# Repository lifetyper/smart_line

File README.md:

就是个通过FT232H芯片，把USB转成SPI、I2C用于硬件调试的小工具，软件使用的是pyftdi。

第一版硬件有点小bug，但实际上使用时并不表现出来。

第二版改成kicad的开源工具了，很难用，所以凑合着用4层板画比较简单，反正嘉立创现在4层板才50块钱。。。。

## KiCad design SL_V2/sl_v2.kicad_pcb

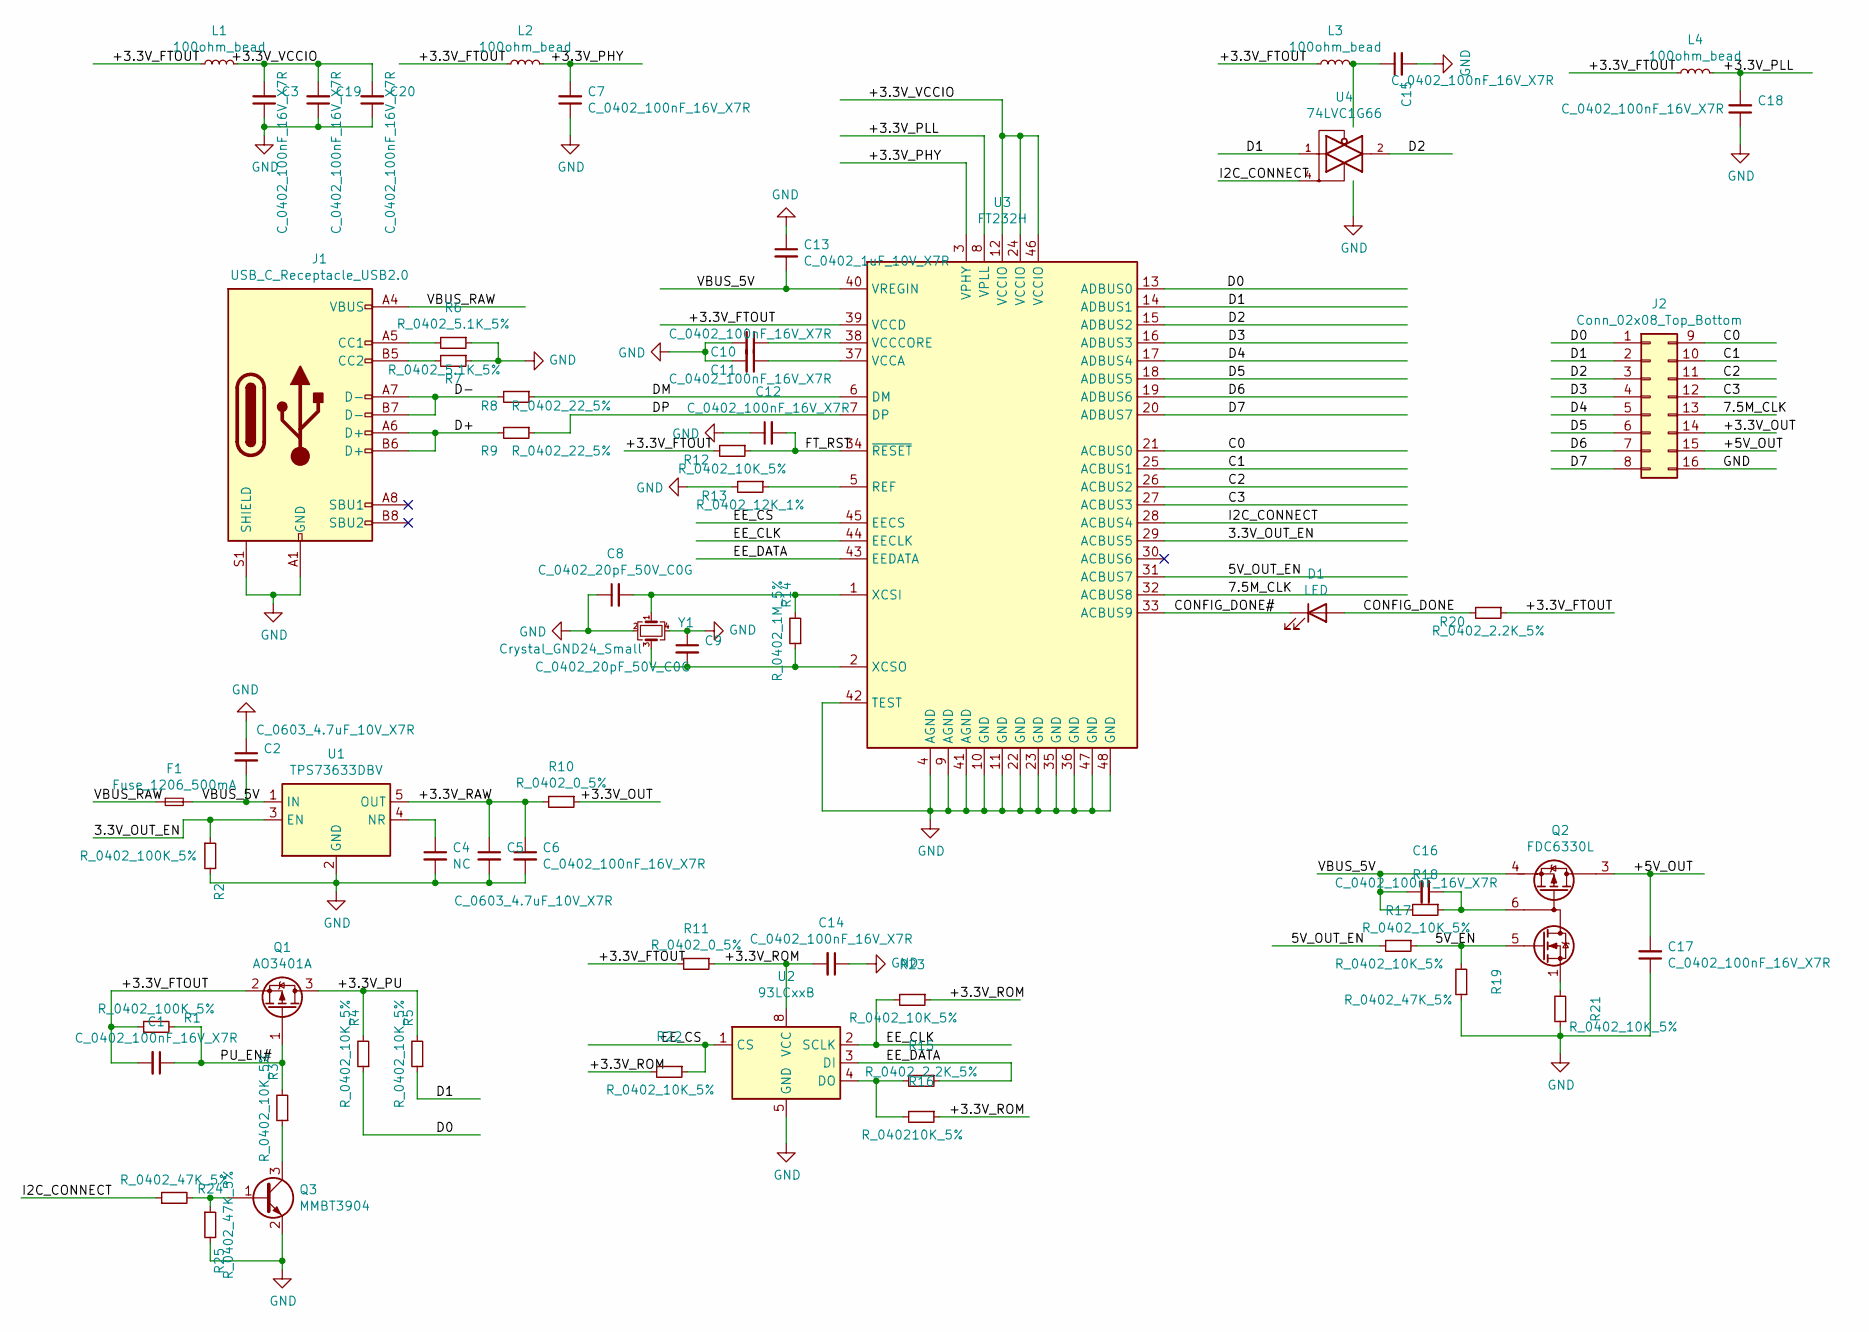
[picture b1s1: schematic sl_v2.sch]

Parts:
C1, C3, C6, C7, C10, C11, C12, C14, C15, C16, C17, C18, C19, C20: C_0402_100nF_16V_X7R; C_0402_1005Metric
C2, C5: C_0603_4.7uF_10V_X7R; C_0603_1608Metric
C4: NC; C_0402_1005Metric
C8, C9: C_0402_20pF_50V_C0G; C_0402_1005Metric
C13: C_0402_1uF_10V_X7R; C_0402_1005Metric
D1: LED; LED_0603_1608Metric
F1: Fuse_1206_500mA; Fuse_1206_3216Metric
J1: USB_C_Receptacle_USB2.0; USB_C_Receptacle_HRO_TYPE-C-31-M-12
J2: Conn_02x08_Top_Bottom; Connector_02X08_SMD_C
L1, L2, L3, L4: 100ohm_bead; L_0402_1005Metric
Q1: AO3401A; SOT-23
Q2: FDC6330L; TSOT-23-6
Q3: MMBT3904; SOT-23
R1, R2: R_0402_100K_5%; R_0402_1005Metric
R3, R4, R5, R12, R17, R18, R21, R22, R23: R_0402_10K_5%; R_0402_1005Metric
R6, R7: R_0402_5.1K_5%; R_0402_1005Metric
R8, R9: R_0402_22_5%; R_0402_1005Metric
R10, R11: R_0402_0_5%; R_0402_1005Metric
R13: R_0402_12K_1%; R_0402_1005Metric
R14: R_0402_1M_5%; R_0402_1005Metric
R15, R20: R_0402_2.2K_5%; R_0402_1005Metric
R16: R_040210K_5%; R_0402_1005Metric
R19, R24, R25: R_0402_47K_5%; R_0402_1005Metric
U1: TPS73633DBV; SOT-23-5
U2: 93LCxxB; SOIC-8_3.9x4.9mm_P1.27mm
U3: FT232H; LQFP-48_7x7mm_P0.5mm
U4: 74LVC1G66; SOT-353_SC-70-5
Y1: Crystal_GND24_Small; Oscillator_SMD_EuroQuartz_XO32-4Pin_3.2x2.5mm

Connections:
/3.3V_OUT_EN: R2.1, U1.3 (EN), U3.29 (ACBUS5)
/5V_EN: Q2.5 (G1), R17.1, R19.2
/5V_OUT_EN: R17.2, U3.31 (ACBUS7)
/7.5M_CLK: J2.13, U3.32 (ACBUS8)
/+3.3V_FTOUT: C1.2, L1.1, L2.1, L3.1, L4.1, Q1.2 (S), R1.1, R11.2, R12.2, R20.1, U3.39 (VCCD)
/+3.3V_PHY: C7.2, L2.2, U3.3 (VPHY)
/+3.3V_PLL: C18.2, L4.2, U3.8 (VPLL)
/+3.3V_PU: Q1.3 (D), R4.2, R5.2
/+3.3V_RAW: C5.1, C6.1, R10.2, U1.5 (OUT)
/+3.3V_ROM: C14.2, R11.1, R16.1, R22.2, R23.1, U2.8 (VCC)
/+3.3V_VCCIO: C3.2, C19.2, C20.2, L1.2, U3.12 (VCCIO), U3.24 (VCCIO), U3.46 (VCCIO)
/C0: J2.9, U3.21 (ACBUS0)
/C1: J2.10, U3.25 (ACBUS1)
/C2: J2.11, U3.26 (ACBUS2)
/C3: J2.12, U3.27 (ACBUS3)
/CONFIG_DONE: D1.2 (A), R20.2
/CONFIG_DONE#: D1.1 (K), U3.33 (ACBUS9)
/D0: J2.1, R4.1, U3.13 (ADBUS0)
/D1: J2.2, R5.1, U3.14 (ADBUS1), U4.1
/D2: J2.3, U3.15 (ADBUS2), U4.2
/D3: J2.4, U3.16 (ADBUS3)
/D4: J2.5, U3.17 (ADBUS4)
/D5: J2.6, U3.18 (ADBUS5)
/D6: J2.7, U3.19 (ADBUS6)
/D7: J2.8, U3.20 (ADBUS7)
/D+: J1.A6 (D+), J1.B6 (D+), R9.2
/D-: J1.A7 (D-), J1.B7 (D-), R8.2
/DM: R8.1, U3.6 (DM)
/DP: R9.1, U3.7 (DP)
/EE_CLK: R23.2, U2.2 (SCLK), U3.44 (EECLK)
/EE_CS: R22.1, U2.1 (CS), U3.45 (EECS)
/EE_DATA: R15.1, U2.3 (DI), U3.43 (EEDATA)
/FT_RST: C12.2, R12.1, U3.34 (~RESET)
/I2C_CONNECT: R24.1, U3.28 (ACBUS4), U4.4
/PU_EN#: C1.1, Q1.1 (G), R1.2, R3.2
/VBUS_5V: C2.2, C13.2, C16.2, F1.2, Q2.4 (S2), R18.2, U1.1 (IN), U3.40 (VREGIN)
/VBUS_RAW: F1.1, J1.A4 (VBUS), J1.A9 (VBUS), J1.B4 (VBUS), J1.B9 (VBUS)
GND: C2.1, C3.1, C4.2, C5.2, C6.2, C7.1, C8.1, C9.1, C10.2, C11.2, C12.1, C13.1, C14.1, C15.2, C17.1, C18.1, C19.1, C20.1, J1.A1 (GND), J1.A12 (GND), J1.B1 (GND), J1.B12 (GND), J1.S1 (SHIELD), J2.16, Q3.2 (E), R2.2, R6.1, R7.1, R13.2, R19.1, R21.1, R25.2, U1.2 (GND), U2.5 (GND), U3.4 (AGND), U3.9 (AGND), U3.10 (GND), U3.11 (GND), U3.22 (GND), U3.23 (GND), U3.35 (GND), U3.36 (GND), U3.41 (AGND), U3.42 (TEST), U3.47 (GND), U3.48 (GND), U4.3 (GND), Y1.2, Y1.4
unnamed: C4.1, U1.4 (NR)
unnamed: C8.2, R14.2, U3.1 (XCSI), Y1.1
unnamed: C9.2, R14.1, U3.2 (XCSO), Y1.3
unnamed: C10.1, U3.38 (VCCCORE)
unnamed: C11.1, U3.37 (VCCA)
unnamed: C16.1, Q2.6 (D1), R18.1
unnamed: J1.A5 (CC1), R6.2
unnamed: J1.B5 (CC2), R7.2
unnamed: Q2.1 (S1), R21.2
unnamed: Q3.1 (B), R24.2, R25.1
unnamed: Q3.3 (C), R3.1
unnamed: R13.1, U3.5 (REF)
unnamed: R15.2, R16.2, U2.4 (DO)
VCC: C15.1, L3.2, U4.5 (VCC)

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
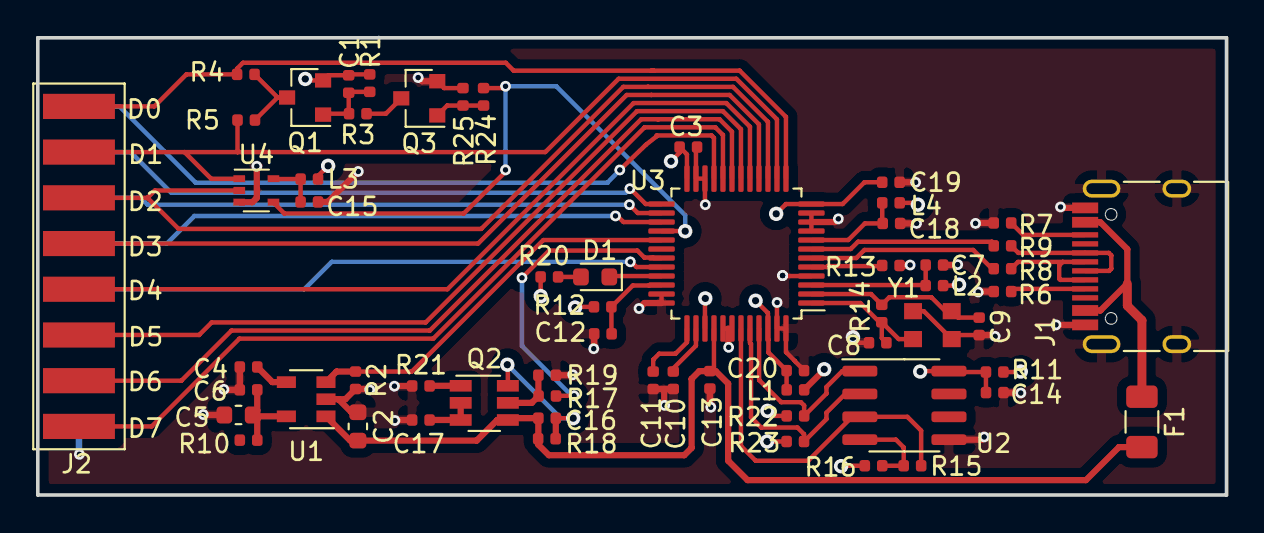
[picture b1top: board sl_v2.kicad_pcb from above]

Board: 4 copper layers, 66.0 x 25.4 mm, 61 parts (0 on the bottom side), 53 nets.

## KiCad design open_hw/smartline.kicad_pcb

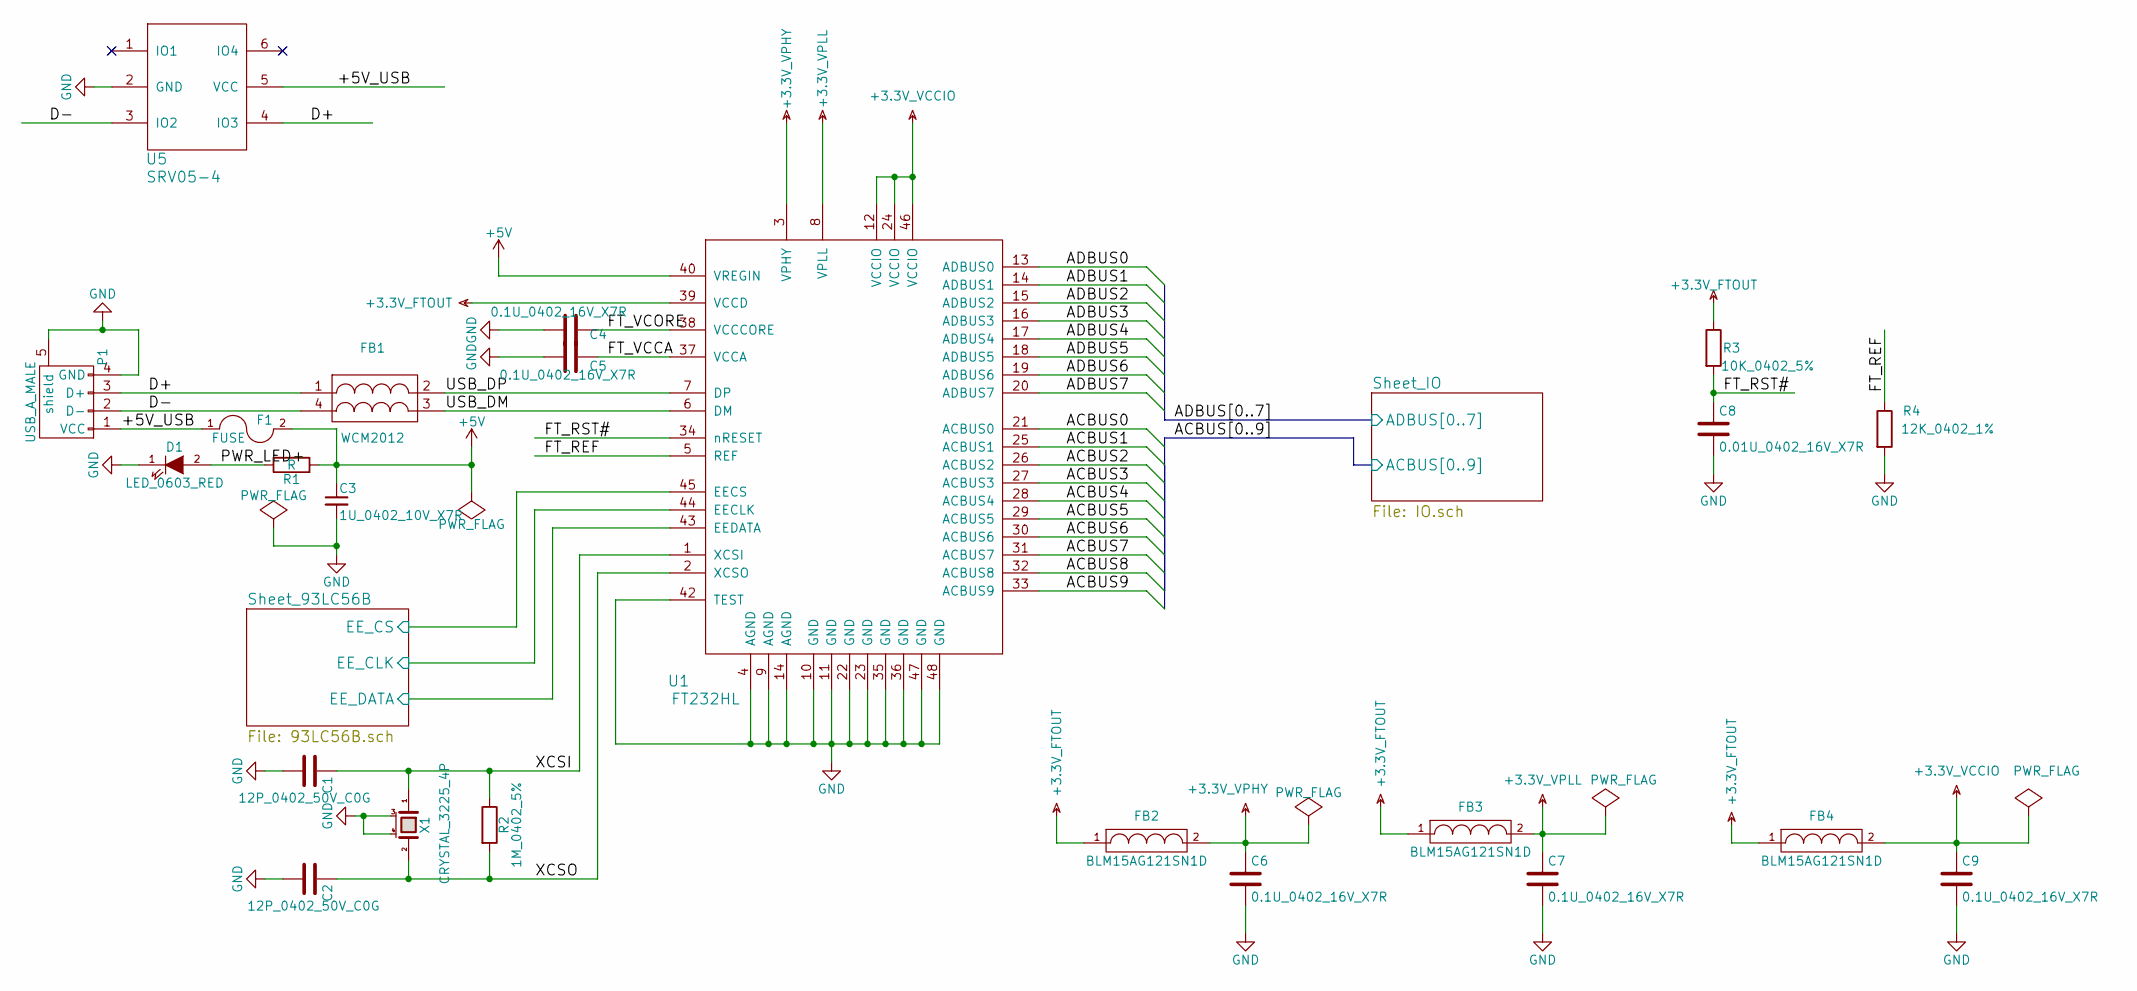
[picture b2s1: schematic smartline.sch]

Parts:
C1, C2: 12P_0402_50V_C0G; C_0402
C3: 1U_0402_10V_X7R; C_0402
C4, C5, C6, C7, C9: 0.1U_0402_16V_X7R; C_0402
C8: 0.01U_0402_16V_X7R; C_0402
D1: LED_0603_RED; LED_0603
F1: FUSE; Fuse_SMD1206_Reflow
FB1: WCM2012; WCM2012_4P
FB2, FB3, FB4: BLM15AG121SN1D; C_0402
P1: USB_A_MALE; USB_A_SMD
R1: R; R_0402
R2: 1M_0402_5%; R_0402
R3: 10K_0402_5%; R_0402
R4: 12K_0402_1%; R_0402
U1: FT232HL; LQFP-48_7x7mm_Pitch0.5mm
U5: SRV05-4; SOT-23-6
X1: CRYSTAL_3225_4P; Crystall_3225_4P

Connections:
+3.3V_FTOUT: FB2.1, FB3.1, FB4.1, R3.1, U1.39 (VCCD); also elsewhere on the board
+3.3V_VCCIO: C9.1, FB4.2, U1.12 (VCCIO), U1.24 (VCCIO), U1.46 (VCCIO)
+3.3V_VPHY: C6.1, FB2.2, U1.3 (VPHY)
+3.3V_VPLL: C7.1, FB3.2, U1.8 (VPLL)
+5V: C3.1, F1.2, R1.1, U1.40 (VREGIN); also elsewhere on the board
/+5V_USB: F1.1, P1.1 (VCC), U5.5 (VCC)
/ACBUS0: U1.21 (ACBUS0); also elsewhere on the board
/ACBUS1: U1.25 (ACBUS1); also elsewhere on the board
/ACBUS2: U1.26 (ACBUS2); also elsewhere on the board
/ACBUS3: U1.27 (ACBUS3); also elsewhere on the board
/ACBUS4: U1.28 (ACBUS4); also elsewhere on the board
/ACBUS5: U1.29 (ACBUS5); also elsewhere on the board
/ACBUS6: U1.30 (ACBUS6); also elsewhere on the board
/ACBUS7: U1.31 (ACBUS7); also elsewhere on the board
/ACBUS8: U1.32 (ACBUS8); also elsewhere on the board
/ACBUS9: U1.33 (ACBUS9); also elsewhere on the board
/ADBUS0: U1.13 (ADBUS0); also elsewhere on the board
/ADBUS2: U1.15 (ADBUS2); also elsewhere on the board
/ADBUS3: U1.16 (ADBUS3); also elsewhere on the board
/ADBUS4: U1.17 (ADBUS4); also elsewhere on the board
/ADBUS5: U1.18 (ADBUS5); also elsewhere on the board
/ADBUS6: U1.19 (ADBUS6); also elsewhere on the board
/ADBUS7: U1.20 (ADBUS7); also elsewhere on the board
/D+: FB1.1, P1.3 (D+), U5.4 (IO3)
/D-: FB1.4, P1.2 (D-), U5.3 (IO2)
/FT_REF: R4.1, U1.5 (REF)
/FT_RST#: C8.1, R3.2, U1.34 (nRESET)
/FT_VCCA: C5.1, U1.37 (VCCA)
/FT_VCORE: C4.1, U1.38 (VCCCORE)
/PWR_LED+: D1.2 (A), R1.2
/Sheet_93LC56B/EE_CLK: U1.44 (EECLK); also elsewhere on the board
/Sheet_93LC56B/EE_CS: U1.45 (EECS); also elsewhere on the board
/Sheet_93LC56B/EE_DATA: U1.43 (EEDATA); also elsewhere on the board
/USB_DM: FB1.3, U1.6 (DM)
/USB_DP: FB1.2, U1.7 (DP)
/XCSI: C1.1, R2.1, U1.1 (XCSI), X1.1
/XCSO: C2.1, R2.2, U1.2 (XCSO), X1.2

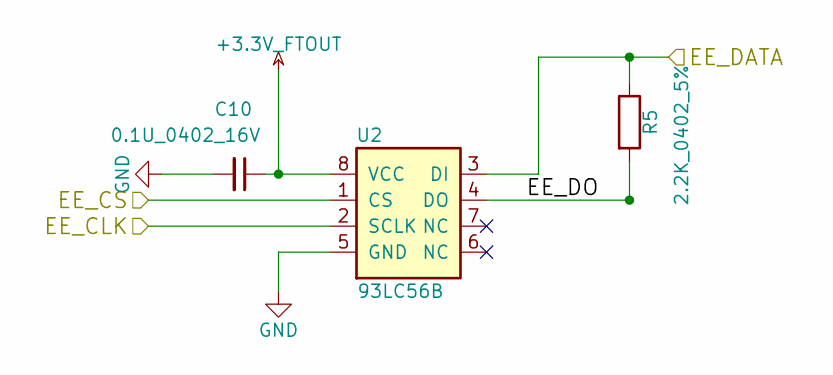
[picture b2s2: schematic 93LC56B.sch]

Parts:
C10: 0.1U_0402_16V; C_0402
R5: 2.2K_0402_5%; R_0402
U2: 93LC56B; SOIC-8_3.9x4.9mm_Pitch1.27mm

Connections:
+3.3V_FTOUT: C10.1, U2.8 (VCC); also elsewhere on the board
/Sheet_93LC56B/EE_CLK: U2.2 (SCLK); also elsewhere on the board
/Sheet_93LC56B/EE_CS: U2.1 (CS); also elsewhere on the board
/Sheet_93LC56B/EE_DATA: R5.1, U2.3 (DI); also elsewhere on the board
/Sheet_93LC56B/EE_DO: R5.2, U2.4 (DO)

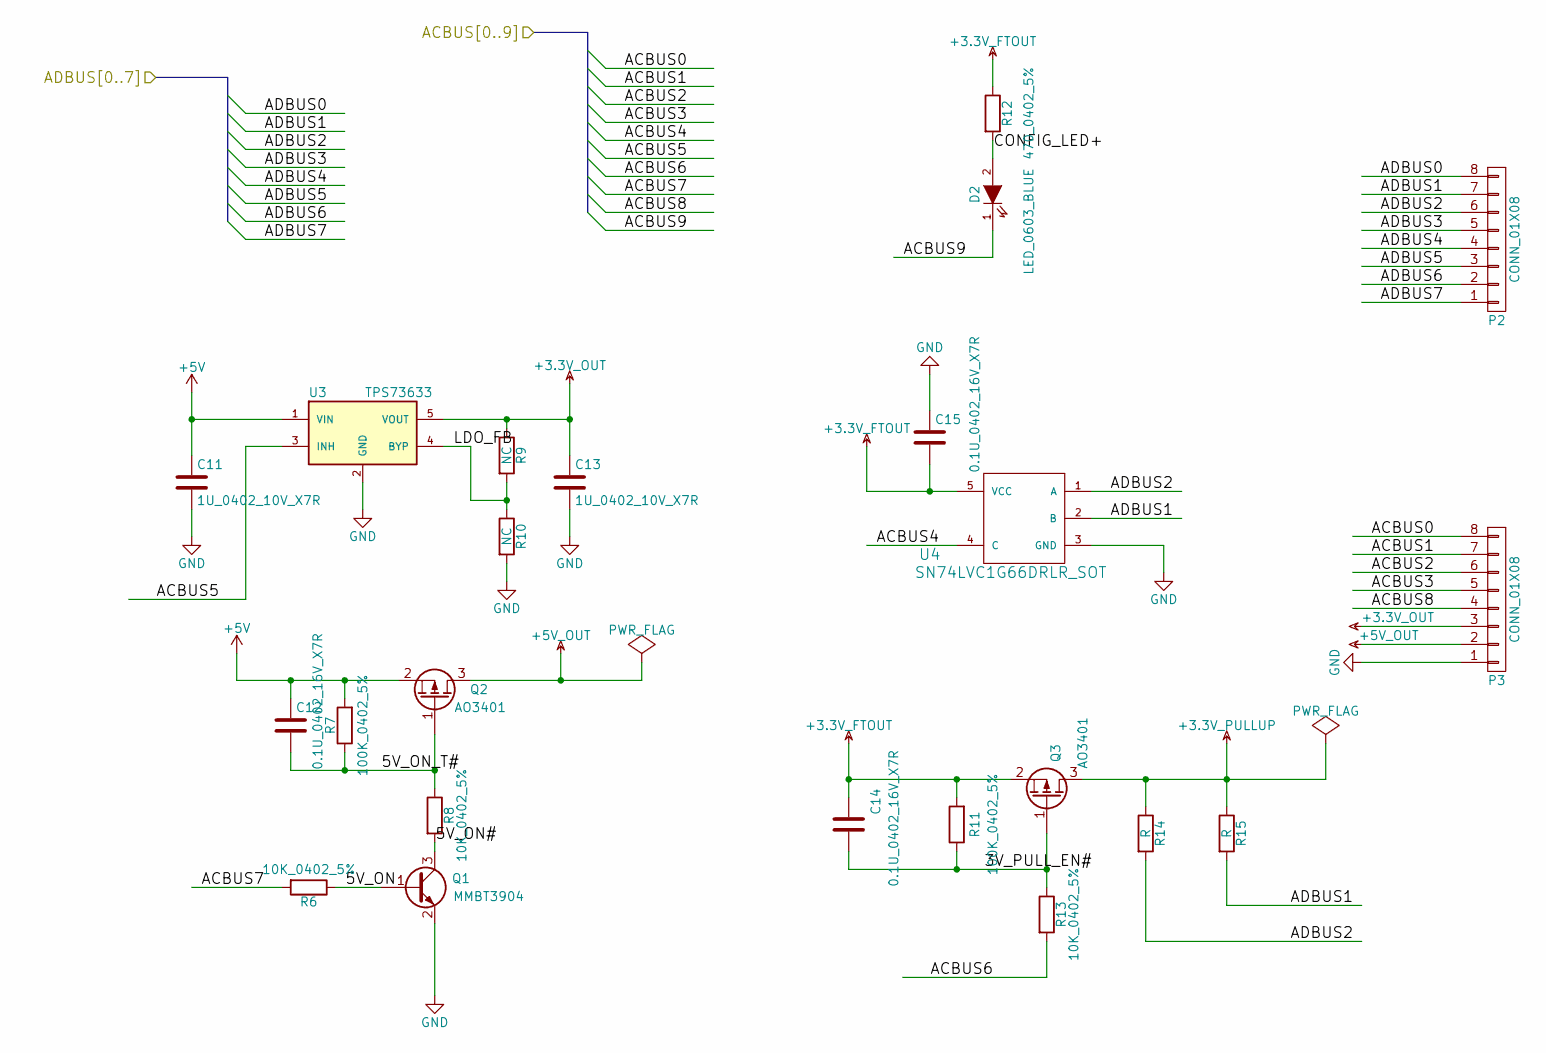
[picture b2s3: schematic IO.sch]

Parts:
C11, C13: 1U_0402_10V_X7R; C_0402
C12, C14, C15: 0.1U_0402_16V_X7R; C_0402
D2: LED_0603_BLUE; LED_0603
P2, P3: CONN_01X08; Pin_Header_SMD_1x08
Q1: MMBT3904; SOT-23
Q2, Q3: AO3401; SOT-23
R6, R8, R13: 10K_0402_5%; R_0402
R7, R11: 100K_0402_5%; R_0402
R9, R10: NC; R_0402
R12: 470_0402_5%; R_0402
R14, R15: R; R_0402
U3: TPS73633; SOT-23-5
U4: SN74LVC1G66DRLR_SOT; SC-70-5

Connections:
+3.3V_FTOUT: C14.1, C15.2, Q3.2 (S), R11.2, R12.1, U4.5 (VCC); also elsewhere on the board
+3.3V_OUT: C13.1, P3.3, R9.1, U3.5 (VOUT)
+3.3V_PULLUP: Q3.3 (D), R14.1, R15.1
+5V: C11.1, C12.1, Q2.2 (S), R7.2, U3.1 (VIN); also elsewhere on the board
+5V_OUT: P3.2, Q2.3 (D)
/ACBUS0: P3.8; also elsewhere on the board
/ACBUS1: P3.7; also elsewhere on the board
/ACBUS2: P3.6; also elsewhere on the board
/ACBUS3: P3.5; also elsewhere on the board
/ACBUS4: U4.4 (C); also elsewhere on the board
/ACBUS5: U3.3 (INH); also elsewhere on the board
/ACBUS6: R13.2; also elsewhere on the board
/ACBUS7: R6.2; also elsewhere on the board
/ACBUS8: P3.4; also elsewhere on the board
/ACBUS9: D2.1 (K); also elsewhere on the board
/ADBUS0: P2.8; also elsewhere on the board
/ADBUS2: P2.6, R14.2, U4.1 (A); also elsewhere on the board
/ADBUS3: P2.5; also elsewhere on the board
/ADBUS4: P2.4; also elsewhere on the board
/ADBUS5: P2.3; also elsewhere on the board
/ADBUS6: P2.2; also elsewhere on the board
/ADBUS7: P2.1; also elsewhere on the board
/Sheet_IO/3V_PULL_EN#: C14.2, Q3.1 (G), R11.1, R13.1
/Sheet_IO/5V_ON: Q1.1 (B), R6.1
/Sheet_IO/5V_ON#: Q1.3 (C), R8.2
/Sheet_IO/5V_ON_T#: C12.2, Q2.1 (G), R7.1, R8.1
/Sheet_IO/CONFIG_LED+: D2.2 (A), R12.2
/Sheet_IO/LDO_FB: R9.2, R10.1, U3.4 (BYP)

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
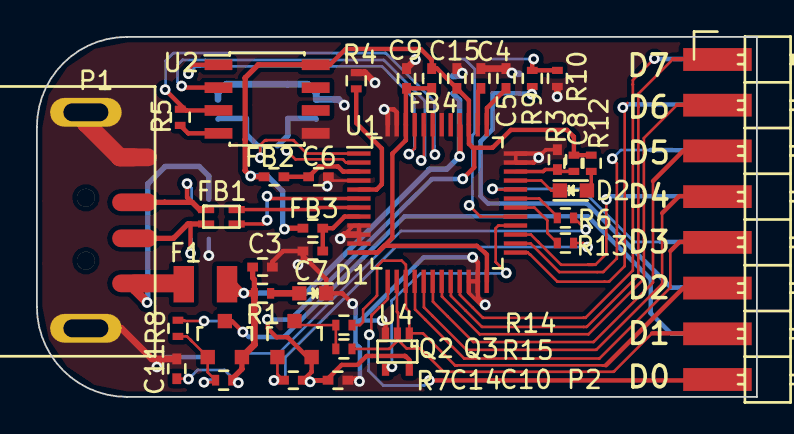
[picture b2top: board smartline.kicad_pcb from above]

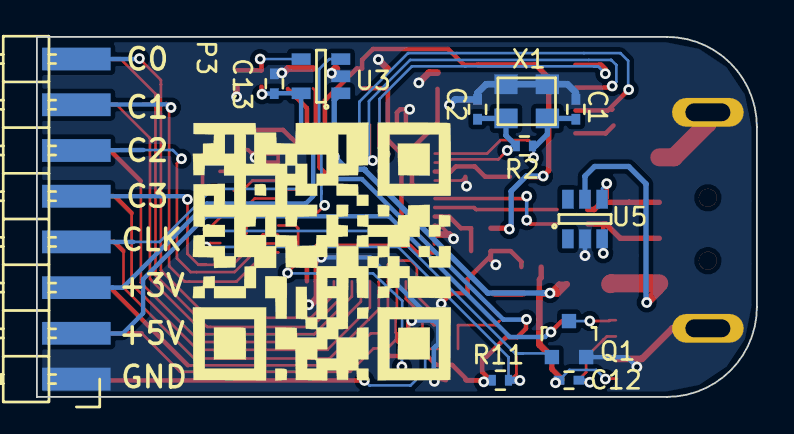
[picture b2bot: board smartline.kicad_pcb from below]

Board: 2 copper layers, 40.0 x 20.0 mm, 49 parts (11 on the bottom side), 49 nets.

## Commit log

2015-12-28 Init
    Nothing
2015-12-28 add bom
2016-01-03 add lcm1602 library and test code
    add lcm1602 library and test code
2016-01-05 add at24c04 library and combined test code
2016-01-07 fix for x01 hardware io config
2016-01-08 add ds1307 library
2016-01-25 add open hardware version
2016-01-25 fix:move back ft232hl
2016-01-25 change zone fill to full hatch
2016-01-25 0125_gerber_out
2016-01-25 Revert "0125_gerber_out"
    This reverts commit b63fd5105e898909c3a391913cbdba684720f112.
2016-01-25 increase text size to 1mm*1mm
2016-04-14 no message
2020-08-15 add full opensource verion hardware SL_V2
2020-08-19 fix sl v2 connection
